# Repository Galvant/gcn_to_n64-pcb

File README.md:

GCN to N64 PCB
==============

This repository contains the KiCAD PCB project files for the Gamecube controller
to Nintendo 64 adapter.

The associated firmware project can be found on GitHub at 
https://github.com/brownan/Gamecube-N64-Controller

Pre-assembled boards will be available shortly at [Galvant Industries](www.galvant.ca)

Project Details
---------------

This simple circuit board allows one to use a Nintendo Gamecube controller with a Nintendo 64 console. The primary motivation for this is simple: The Gamecube controller is far superior to the N64 one, especially the analogue sticks. As N64 controllers age, their analogue sticks become loose, eventually losing the ability the fully actuate which can prevent in-game characters from being able to run/preform tight turns/etc.

The board is a fairly simple design featuring an Atmel ATMega328 with the Arduino bootloader loaded on. Located beside each of the through-holes for the cables are mechanical stress relief holes to affix the cables down.

The best place to source the N64 and GCN connectors and cables will probably be to just buy an extension cable off eBay or something and cut the cable down. In addition, you will then need to map which conductor corresponds to which connector pin number, and thus which conductor goes where on the circuit board. A multimeter will be best for this as I found my extension cable did not have the same pin-cable colouring scheme as the official Nintendo controllers do.

The current firmware maps the X and Y buttons to C-left and C-right, and the C-stick straight maps to the C-buttons. This may be changed in the future in order to provide A-B turbo functionality to the XY buttons, while a Smash Bros specific buttons mapping could also be made to closer emulate the control scheme in Melee (ie C-stick for smash attacks, XY for jumping, etc).

Controller Rumble
-----------------

Technically the firmware does support driving the Gamecube controller's rumble motor, but this is not really supported by this PCB. The reason is because, according to my research, the N64 is not able to provide enough power through its ports to drive it. The N64 outputs 3.3V while the Gamecube outputs 3.3V and 5V, with the 5V to drive the rumble motor. While I do understand that I can step-up the 3.3V from the N64 to the 5V for the rumble motor, I don't know if the N64 can handle outputting the required power. This is not something I particularly feel like testing as I don't want to accidently burn out my N64 controller ports.

Video
-----

A basic video of the adapter in action can be [found on the author's YouTube channel](http://www.youtube.com/watch?v=secM9QJF3xM).

License
-------

This work is released under the Creative Commons Attribution-Sharealike 3.0 license. 
See http://creativecommons.org/licenses/by-sa/3.0/ or the included license/LICENSE.TXT file 
for more information.

Other
-----

All Nintendo trademarks are theirs, etc etc.

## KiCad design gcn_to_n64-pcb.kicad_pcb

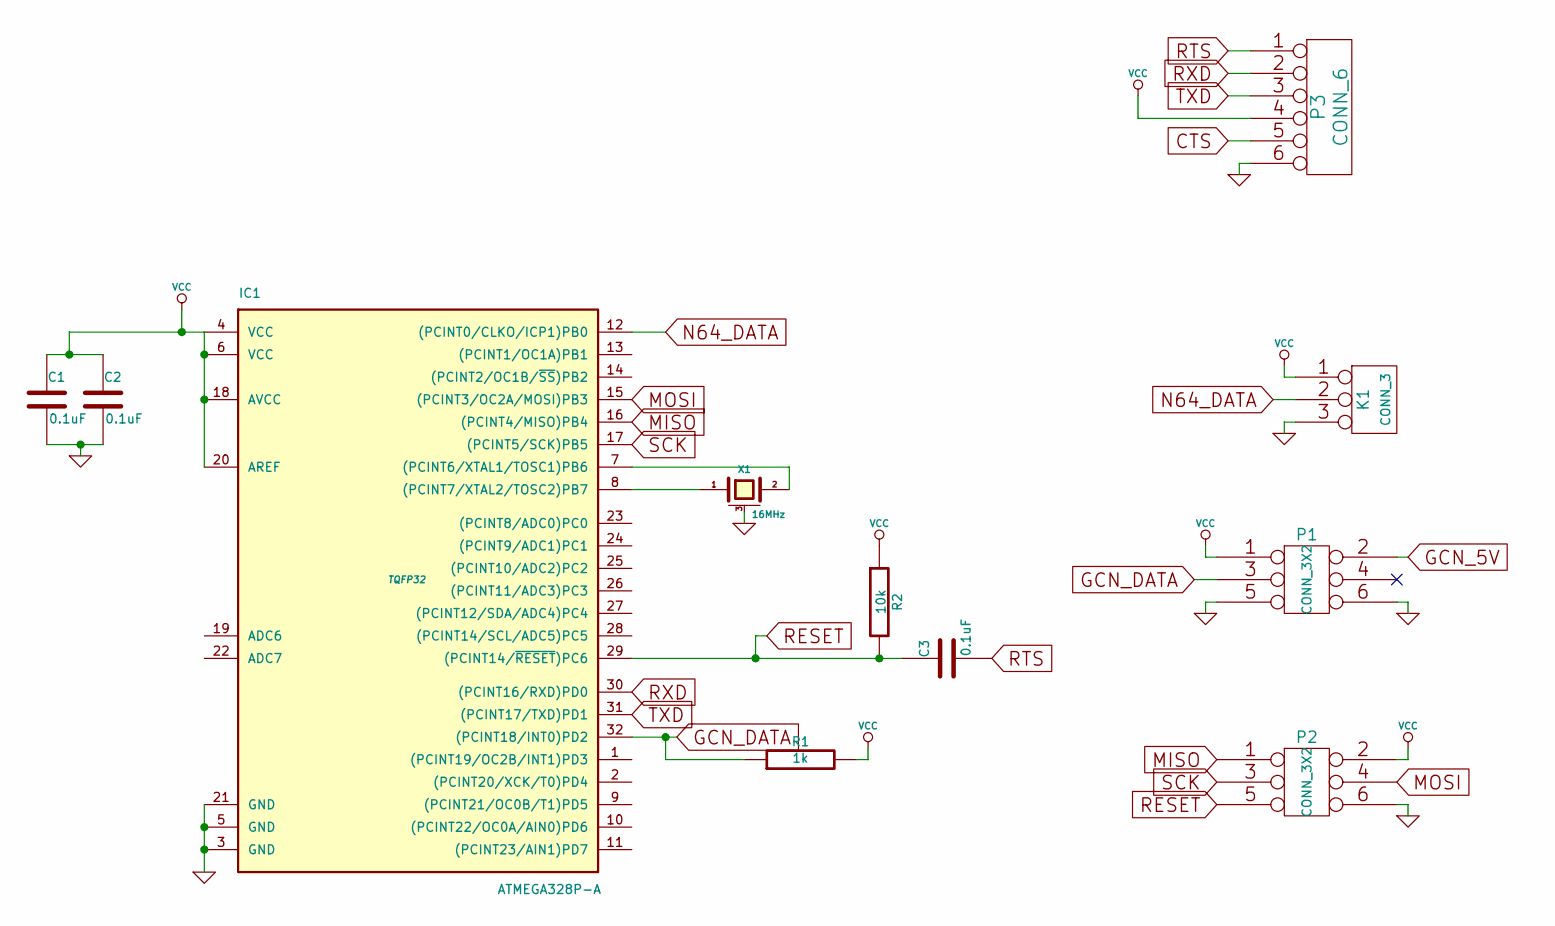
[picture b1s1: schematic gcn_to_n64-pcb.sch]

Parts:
C1, C2, C3: 0.1uF
IC1: ATMEGA328P-A; TQFP32
K1: CONN_3
P1, P2: CONN_3X2
P3: CONN_6
R1: 1k
R2: 10k
X1: 16MHz

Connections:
CTS: P3.5
GCN_5V: P1.2
GCN_DATA: IC1.32 ((PCINT18/INT0)PD2), P1.3, R1.1
GND: C1.2, C2.2, IC1.3 (GND), IC1.5 (GND), IC1.21 (GND), K1.3, P1.5, P1.6, P2.6, P3.6, X1.3 (case)
MISO: IC1.16 ((PCINT4/MISO)PB4), P2.1
MOSI: IC1.15 ((PCINT3/OC2A/MOSI)PB3), P2.4
N64_DATA: IC1.12 ((PCINT0/CLKO/ICP1)PB0), K1.2 (PM)
unnamed: IC1.7 ((PCINT6/XTAL1/TOSC1)PB6), X1.2
unnamed: IC1.8 ((PCINT7/XTAL2/TOSC2)PB7), X1.1
RESET: C3.1, IC1.29 ((PCINT14/~RESET~)PC6), P2.5, R2.2
RTS: C3.2, P3.1
RXD: IC1.30 ((PCINT16/RXD)PD0), P3.2
SCK: IC1.17 ((PCINT5/SCK)PB5), P2.3
TXD: IC1.31 ((PCINT17/TXD)PD1), P3.3
VCC: C1.1, C2.1, IC1.4 (VCC), IC1.6 (VCC), IC1.18 (AVCC), IC1.20 (AREF), K1.1, P1.1, P2.2, P3.4, R1.2, R2.1

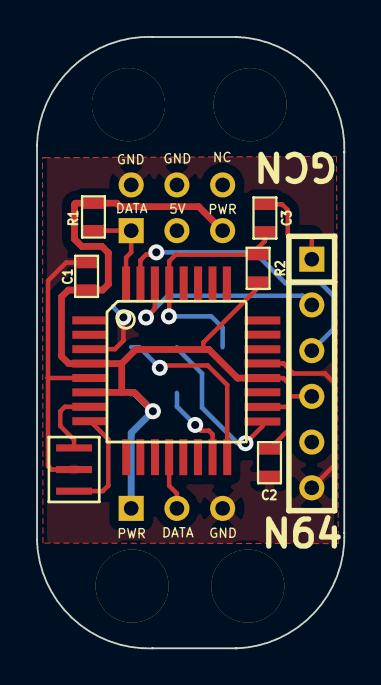
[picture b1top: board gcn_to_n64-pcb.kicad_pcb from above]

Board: 2 copper layers, 17.1 x 34.0 mm, 15 parts (1 on the bottom side), 13 nets.

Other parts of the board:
1PIN, 1PIN#2, 1PIN#3, 1PIN#4: P***; 1pin

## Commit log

2014-09-10 Added license
2014-09-10 Initial README.md commit
2014-09-10 Added youtube video link to readme
2014-09-10 Added note about the controller rumble in readme
